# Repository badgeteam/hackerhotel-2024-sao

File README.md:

# HackerHotel 2024 stuff

Untested, might explode, you've been warned.

## License

The artwork featured in this hardware design has been designed by Nikolett S. from tilde.industries.

The electronics have been designed by Renze Nicolai from Nicolai Electronics.

This hardware design may be used under the terms of the [CERN-OHL-P](LICENSE) license.

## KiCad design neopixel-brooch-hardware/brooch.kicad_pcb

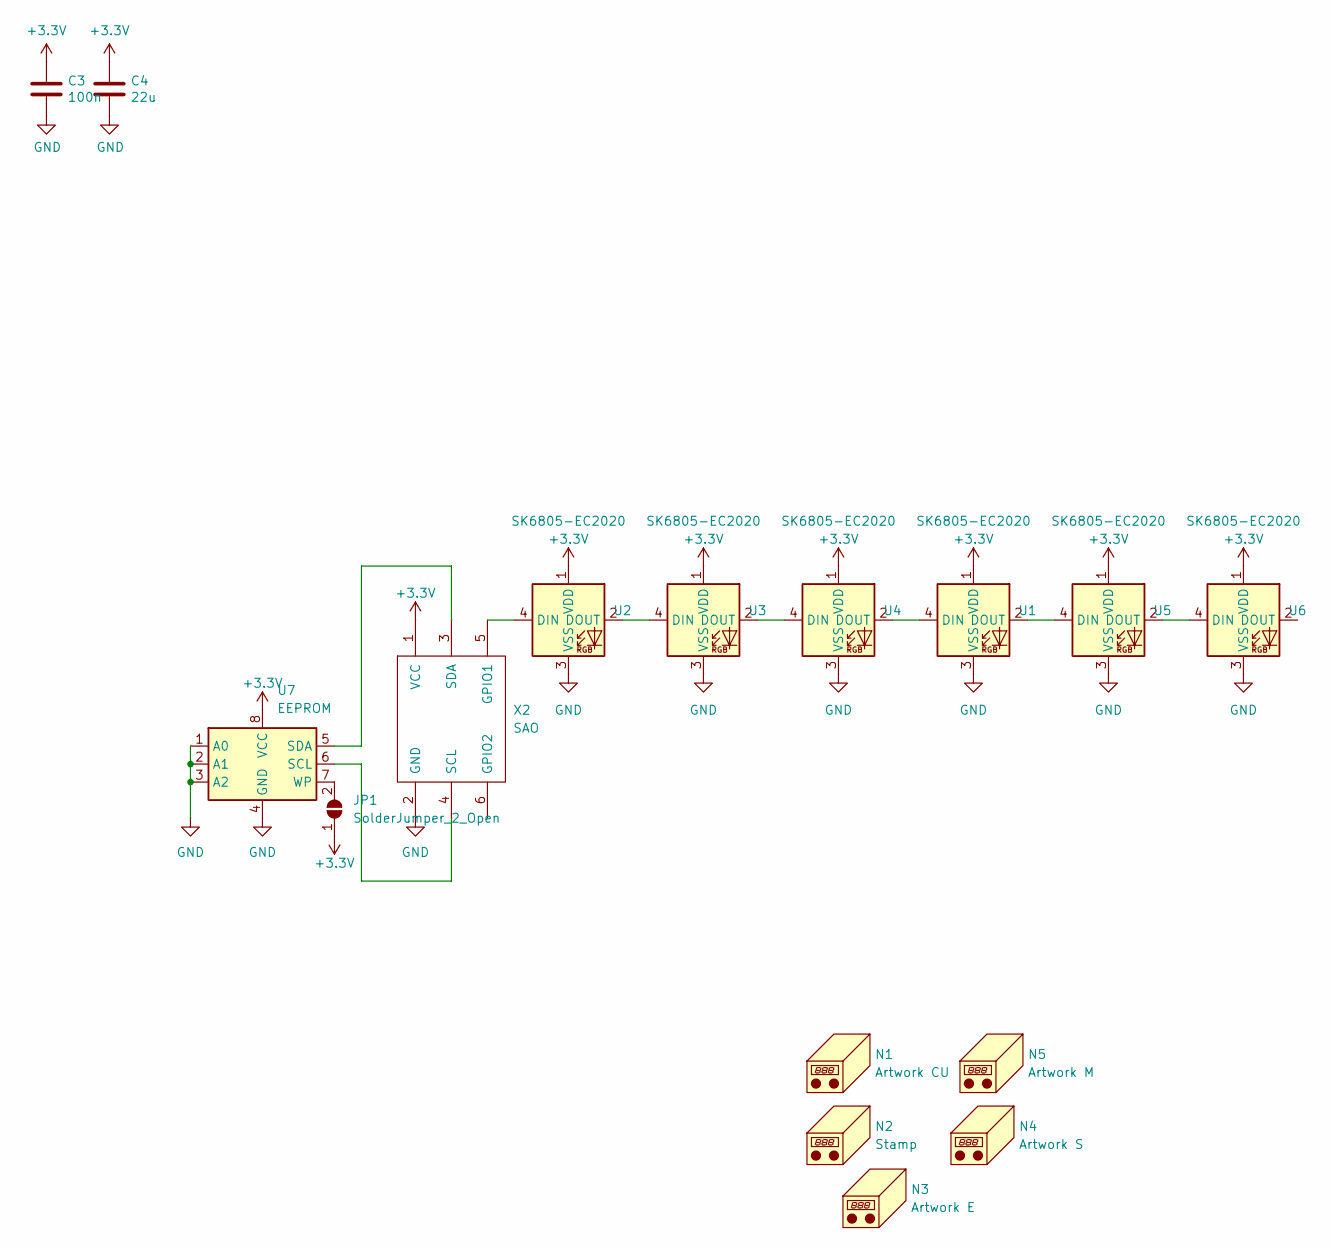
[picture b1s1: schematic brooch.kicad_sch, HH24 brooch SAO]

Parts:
C3: 100n; C_0402_1005Metric; LCSC C307331
C4: 22u; C_0805_2012Metric; LCSC C602037
JP1: SolderJumper_2_Open; SolderJumper-2_P1.3mm_Open_Pad1.0x1.5mm
N1: Artwork CU; Brooch_LED_F.Cu
N2: Stamp; stamp
N3: Artwork E; Brooch_EdgeCut
N4: Artwork S; Brooch_F.SilkS
N5: Artwork M; Brooch_F.Mask
U1, U2, U3, U4, U5, U6: SK6805-EC2020; SK6805-EC20; LCSC C2890036
U7: EEPROM; SOIC-8_3.9x4.9mm_P1.27mm
X2: SAO; PinHeader_2x03_P2.54mm_Vertical_SMD

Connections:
+3.3V: C3.1, C4.1, JP1.1 (A), U1.1 (VDD), U2.1 (VDD), U3.1 (VDD), U4.1 (VDD), U5.1 (VDD), U6.1 (VDD), U7.8 (VCC), X2.1 (VCC)
GND: C3.2, C4.2, U1.3 (VSS), U2.3 (VSS), U3.3 (VSS), U4.3 (VSS), U5.3 (VSS), U6.3 (VSS), U7.1 (A0), U7.2 (A1), U7.3 (A2), U7.4 (GND), X2.2 (GND)
unnamed: JP1.2 (B), U7.7 (WP)
unnamed: U1.4 (DIN), U4.2 (DOUT)
unnamed: U1.2 (DOUT), U5.4 (DIN)
unnamed: U2.4 (DIN), X2.5 (GPIO1)
unnamed: U2.2 (DOUT), U3.4 (DIN)
unnamed: U3.2 (DOUT), U4.4 (DIN)
unnamed: U5.2 (DOUT), U6.4 (DIN)
unnamed: U7.6 (SCL), X2.4 (SCL)
unnamed: U7.5 (SDA), X2.3 (SDA)

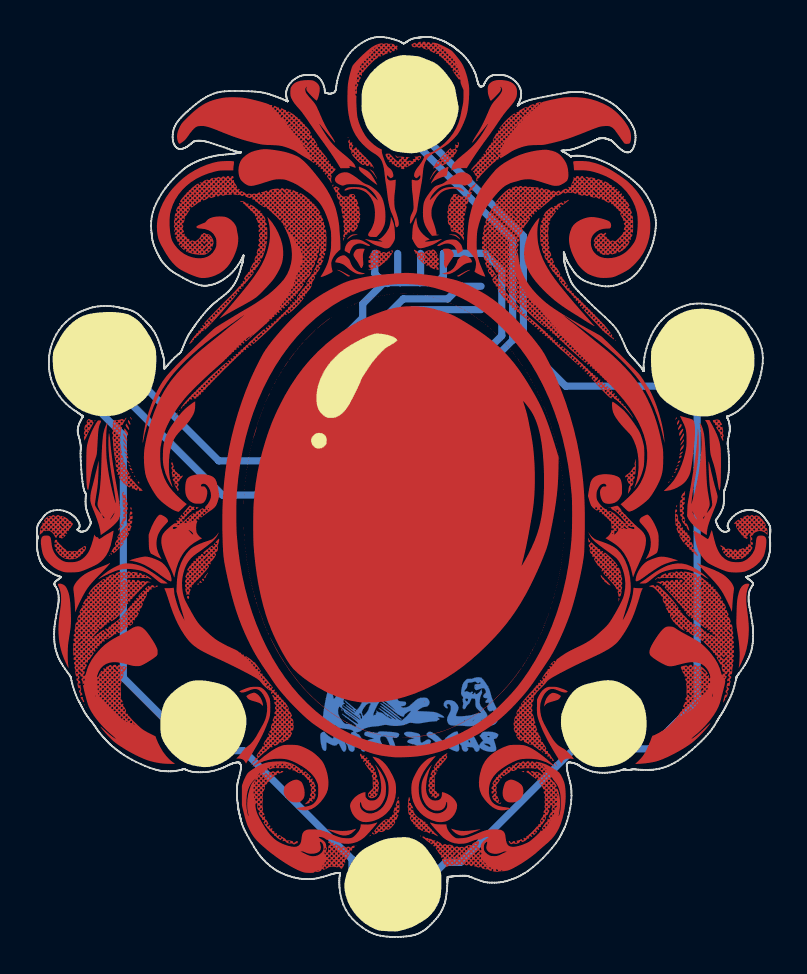
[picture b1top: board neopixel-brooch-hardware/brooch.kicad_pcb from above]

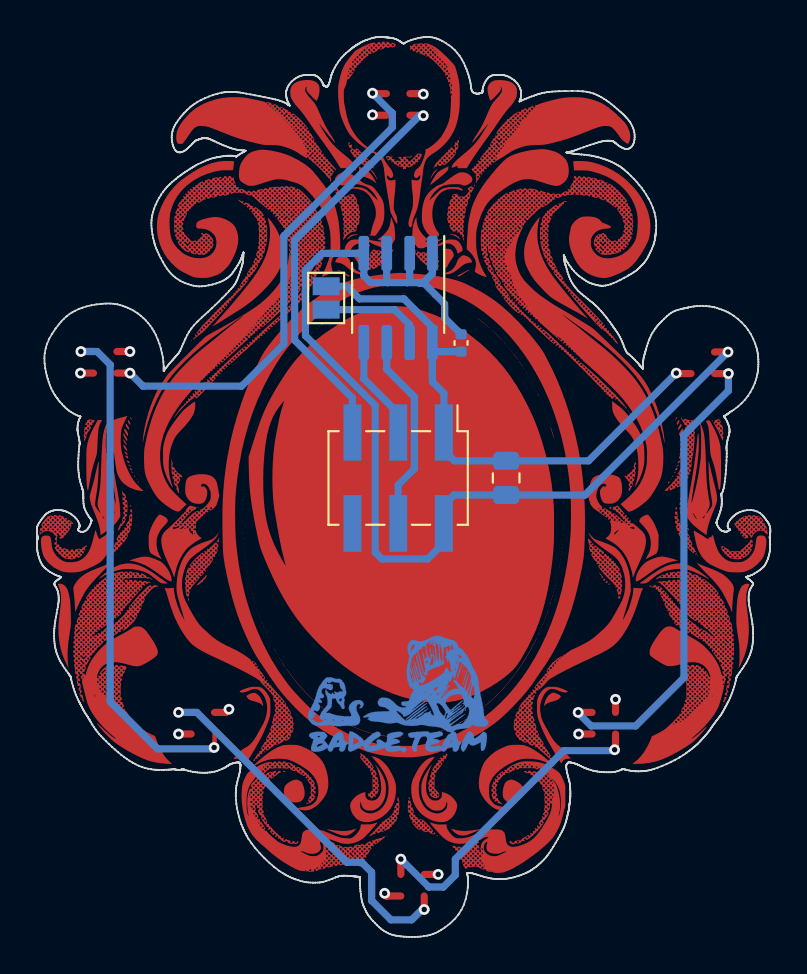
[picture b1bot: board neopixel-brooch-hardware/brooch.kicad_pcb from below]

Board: 4 copper layers, 40.7 x 50.0 mm, 16 parts (6 on the bottom side), 11 nets.

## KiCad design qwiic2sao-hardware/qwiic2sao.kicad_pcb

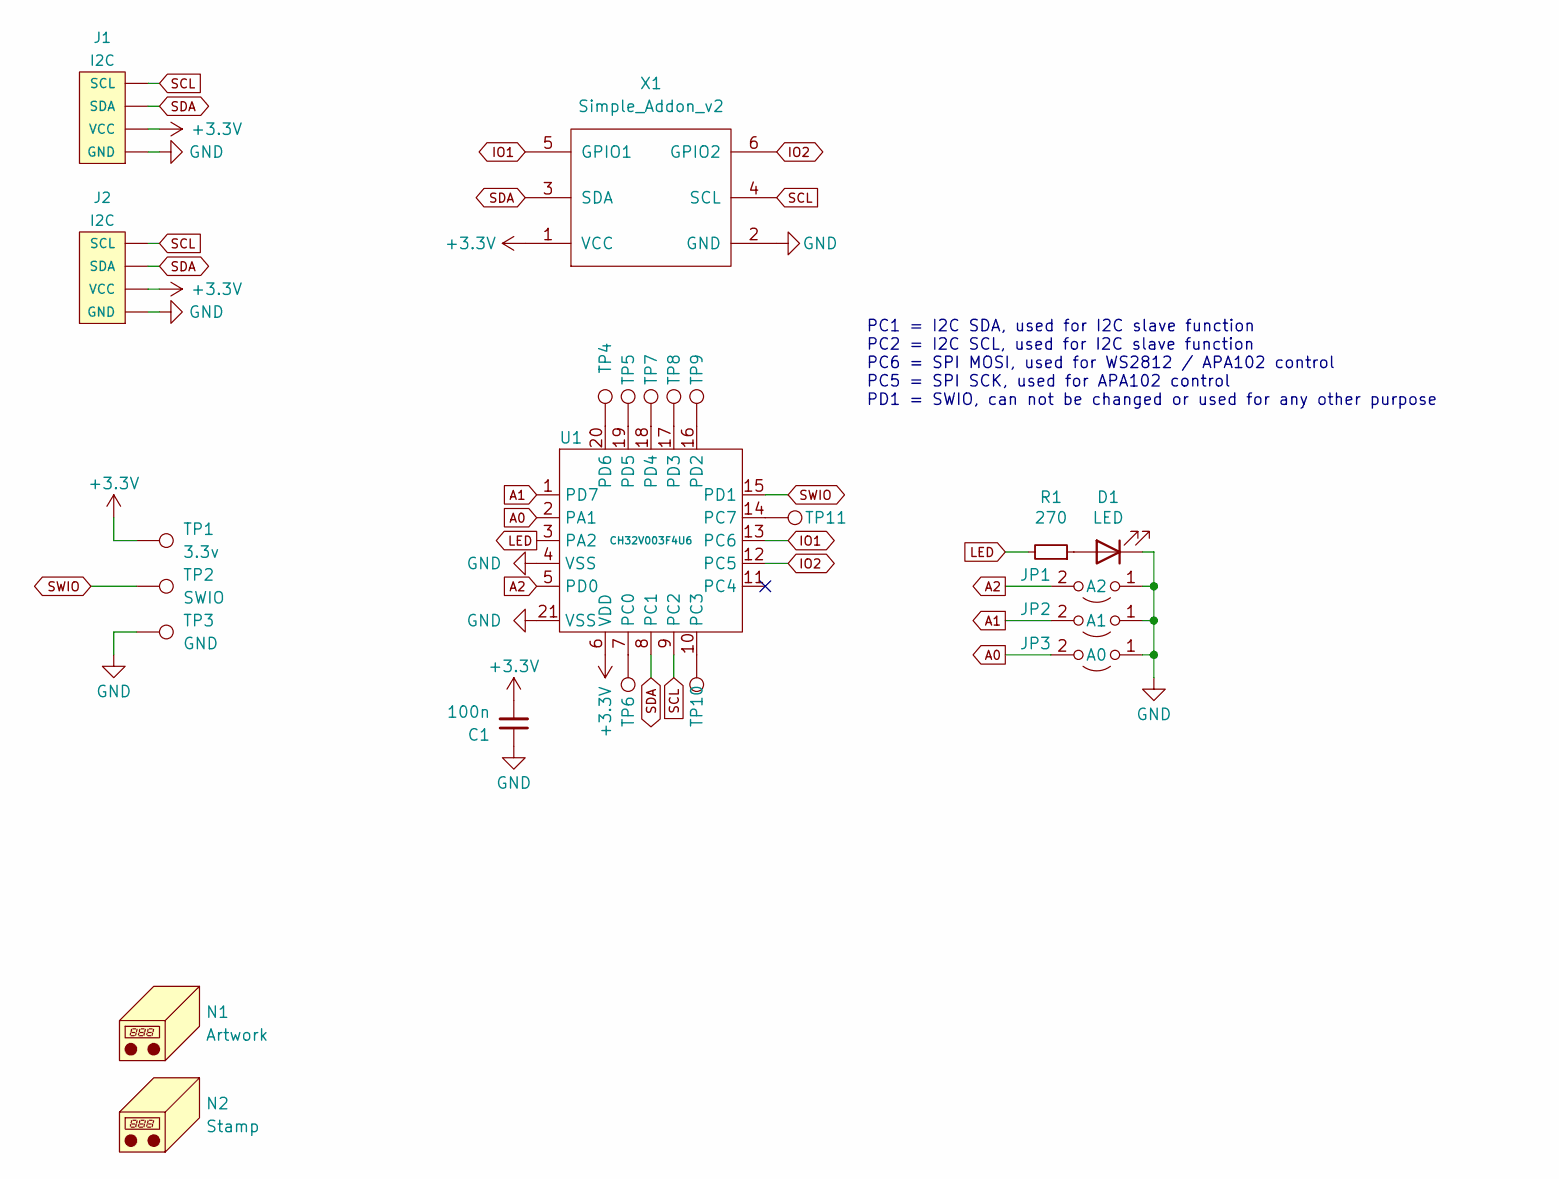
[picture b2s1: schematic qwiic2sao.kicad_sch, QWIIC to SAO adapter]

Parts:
C1: 100n; C_0402_1005Metric
D1: LED; LED_0603_1608Metric; LCSC C264473
J1, J2: I2C; 1X04_1MM_RA_GND; LCSC C160404
JP1: A2; SolderJumper-2_P1.3mm_Open_TrianglePad1.0x1.5mm
JP2: A1; SolderJumper-2_P1.3mm_Open_TrianglePad1.0x1.5mm
JP3: A0; SolderJumper-2_P1.3mm_Open_TrianglePad1.0x1.5mm
N1: Artwork; artwork
N2: Stamp; stamp
R1: 270; R_0402_1005Metric; LCSC C22966
TP1: 3.3v; TestPoint_Pad_D2.0mm
TP2: SWIO; TestPoint_Pad_D2.0mm
TP3: GND; TestPoint_Pad_D2.0mm
TP4, TP5, TP7, TP8, TP9: TestPoint_Pad_D2.0mm
TP6, TP10: TestPoint_Pad_D1.0mm
TP11: 14; TestPoint_Pad_D2.0mm
U1: CH32V003F4U6; QFN-20-1EP_3x3mm_P0.4mm_EP1.65x1.65mm; LCSC C5299908
X1: Simple_Addon_v2; Simple_Addon_v2-BADGE-2x3

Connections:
+3.3V: C1.2, J1.2 (VCC), J2.2 (VCC), TP1.1, U1.6 (VDD), X1.1 (VCC)
A0: JP3.2 (B), U1.2 (PA1)
A1: JP2.2 (B), U1.1 (PD7)
A2: JP1.2 (B), U1.5 (PD0)
GND: C1.1, D1.1 (K), J1.1 (GND), J1.5, J1.6, J2.1 (GND), J2.5, J2.6, JP1.1 (A), JP2.1 (A), JP3.1 (A), TP3.1, U1.4 (VSS), U1.21 (VSS), X1.2 (GND)
IO1: U1.13 (PC6), X1.5 (GPIO1)
IO2: U1.12 (PC5), X1.6 (GPIO2)
LED: R1.2, U1.3 (PA2)
unnamed: D1.2 (A), R1.1
unnamed: TP6.1, U1.7 (PC0)
unnamed: TP10.1, U1.10 (PC3)
unnamed: TP11.1, U1.14 (PC7)
unnamed: TP9.1, U1.16 (PD2)
unnamed: TP8.1, U1.17 (PD3)
unnamed: TP7.1, U1.18 (PD4)
unnamed: TP5.1, U1.19 (PD5)
unnamed: TP4.1, U1.20 (PD6)
SCL: J1.4 (SCL), J2.4 (SCL), U1.9 (PC2), X1.4 (SCL)
SDA: J1.3 (SDA), J2.3 (SDA), U1.8 (PC1), X1.3 (SDA)
SWIO: TP2.1, U1.15 (PD1)

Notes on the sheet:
PC1 = I2C SDA, used for I2C slave function PC2 = I2C SCL, used for I2C slave function PC6 = SPI MOSI, used for WS2812 / APA102 control PC5 = SPI SCK, used for APA102 control PD1 = SWIO, can not be changed or used for any other purpose

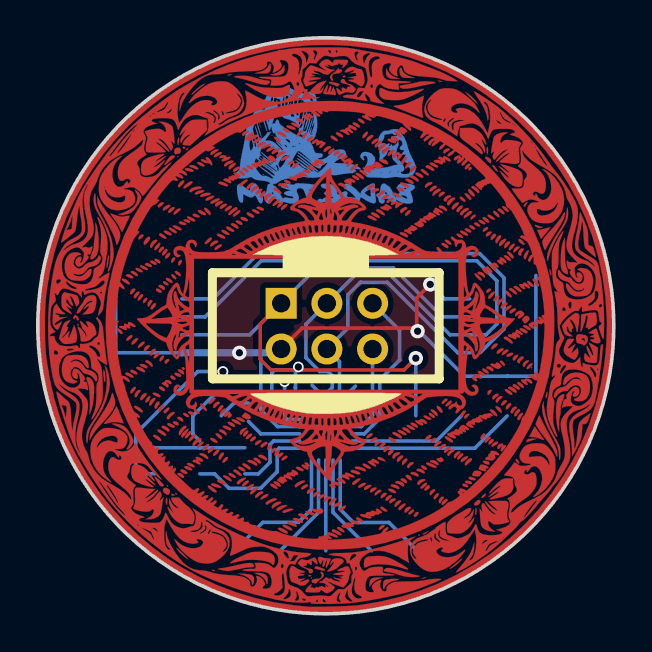
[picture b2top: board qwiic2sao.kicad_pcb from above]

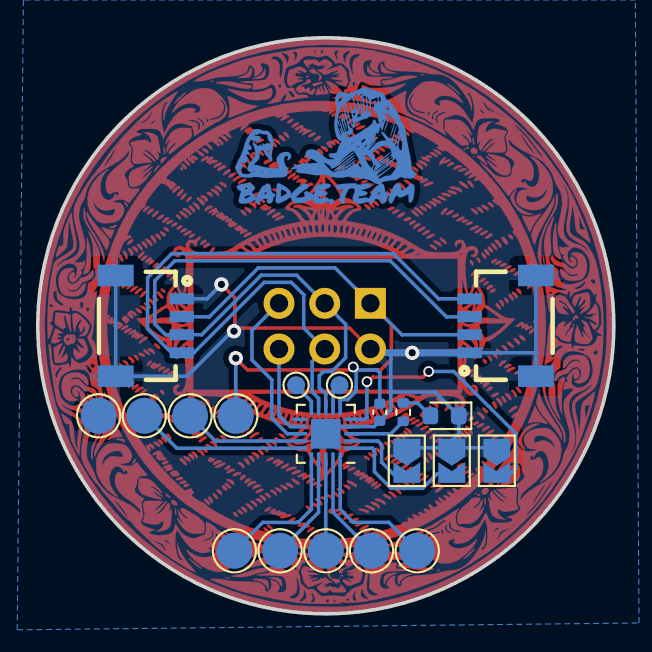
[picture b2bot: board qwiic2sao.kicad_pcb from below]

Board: 2 copper layers, 32.0 x 32.0 mm, 23 parts (21 on the bottom side), 20 nets.

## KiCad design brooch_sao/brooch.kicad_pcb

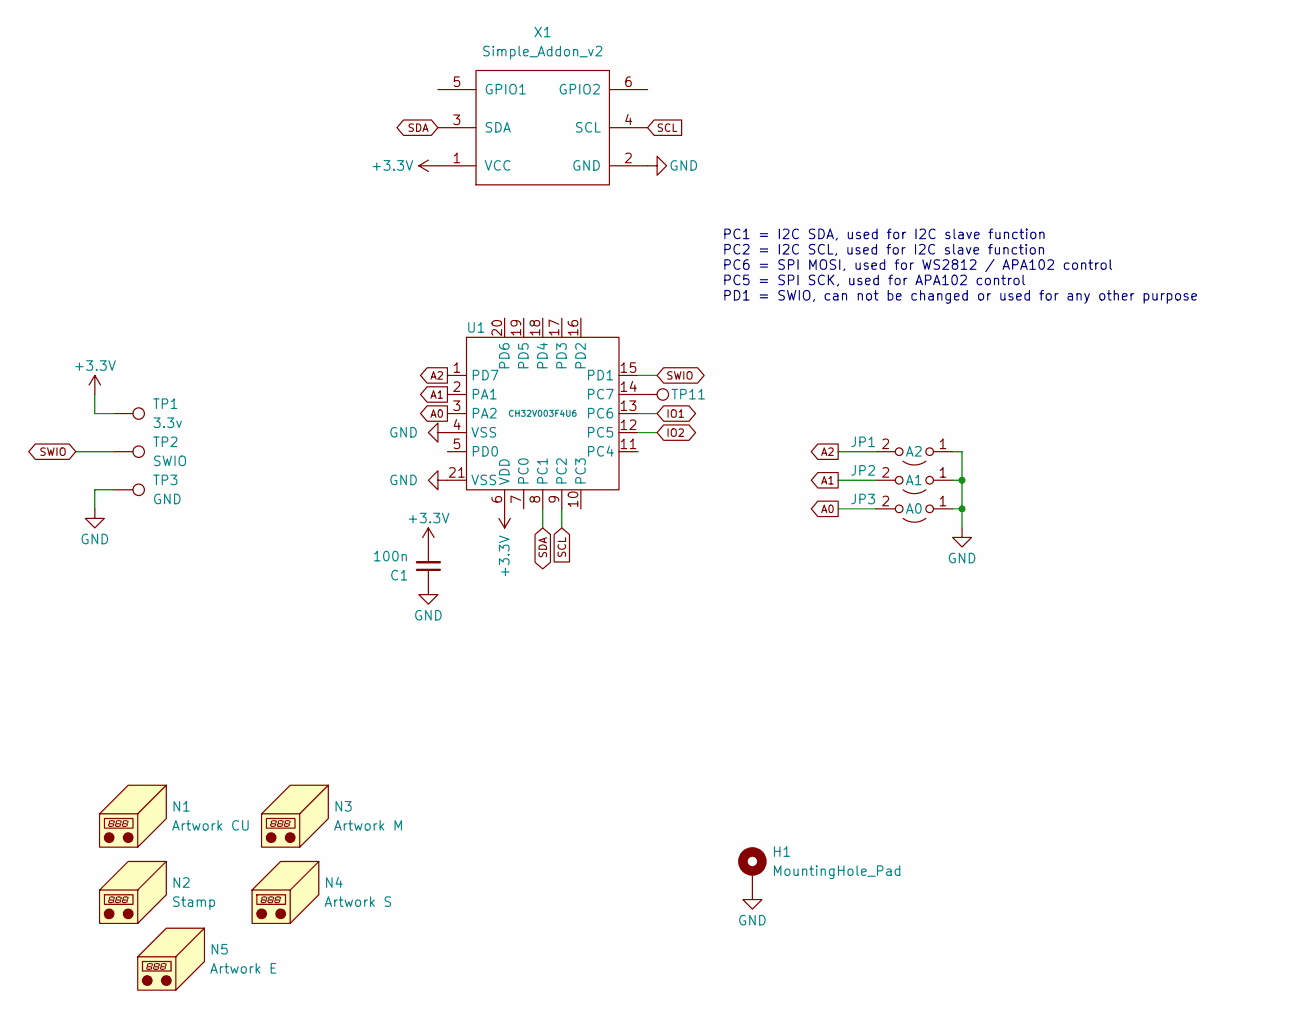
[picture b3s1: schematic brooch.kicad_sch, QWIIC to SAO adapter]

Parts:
C1: 100n; C_0402_1005Metric
H1: MountingHole_Pad; TestPoint_Pad_D5.0mm
JP1: A2; SolderJumper-2_P1.3mm_Open_TrianglePad1.0x1.5mm
JP2: A1; SolderJumper-2_P1.3mm_Open_TrianglePad1.0x1.5mm
JP3: A0; SolderJumper-2_P1.3mm_Open_TrianglePad1.0x1.5mm
N1: Artwork CU; Brooch_F.Cu
N2: Stamp; stamp
N3: Artwork M; Brooch_F.Mask
N4: Artwork S; Brooch_F.SilkS
N5: Artwork E; Brooch_EdgeCut
TP1: 3.3v; TestPoint_Pad_D2.0mm
TP2: SWIO; TestPoint_Pad_D2.0mm
TP3: GND; TestPoint_Pad_D2.0mm
TP11: 14; TestPoint_Pad_D2.0mm
U1: CH32V003F4U6; QFN-20-1EP_3x3mm_P0.4mm_EP1.65x1.65mm; LCSC C5299908
X1: Simple_Addon_v2; PinHeader_2x03_P2.54mm_Vertical_SMD

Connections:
+3.3V: C1.2, TP1.1, U1.6 (VDD), X1.1 (VCC)
A0: JP3.2 (B), U1.3 (PA2)
A1: JP2.2 (B), U1.2 (PA1)
A2: JP1.2 (B), U1.1 (PD7)
GND: C1.1, H1.1, JP1.1 (A), JP2.1 (A), JP3.1 (A), TP3.1, U1.4 (VSS), U1.21 (VSS), X1.2 (GND)
IO1: U1.13 (PC6)
IO2: U1.12 (PC5)
unnamed: TP11.1, U1.14 (PC7)
SCL: U1.9 (PC2), X1.4 (SCL)
SDA: U1.8 (PC1), X1.3 (SDA)
SWIO: TP2.1, U1.15 (PD1)

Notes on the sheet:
PC1 = I2C SDA, used for I2C slave function PC2 = I2C SCL, used for I2C slave function PC6 = SPI MOSI, used for WS2812 / APA102 control PC5 = SPI SCK, used for APA102 control PD1 = SWIO, can not be changed or used for any other purpose

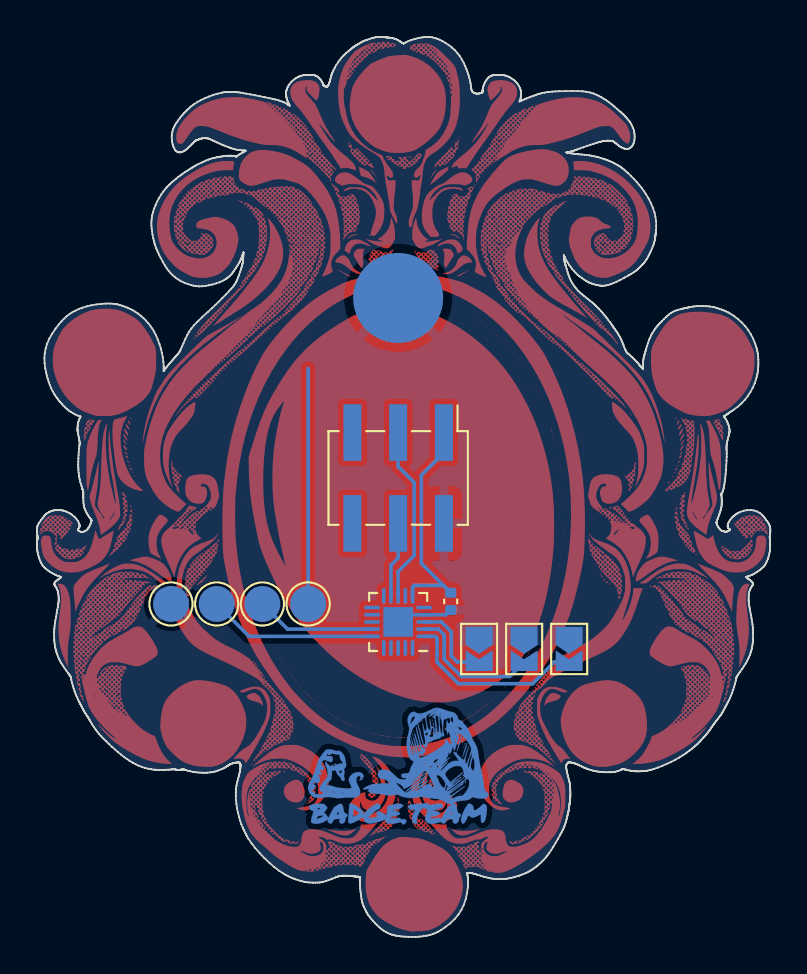
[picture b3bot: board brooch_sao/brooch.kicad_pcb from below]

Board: 2 copper layers, 40.7 x 50.0 mm, 16 parts (12 on the bottom side), 9 nets.

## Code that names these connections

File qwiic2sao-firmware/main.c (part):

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#define I2C_ADDR 0x43

// Address selection jumper pins
#define PIN_AJ0 PA1
#define PIN_AJ1 PD7
#define PIN_AJ2 PD0

// LED pin
#define PIN_LED PA2

// I2C interface pins
#define PIN_SDA PC1
#define PIN_SCL PC2

// SAO GPIO pins
#define PIN_IO1 PC6
#define PIN_IO2 PC5

// GPIO pins on row of testpads
#define PIN_IOA PD2
#define PIN_IOB PD3
#define PIN_IOC PD4
#define PIN_IOD PD5
#define PIN_IOE PD6

// Other GPIO pins
#define PIN_EXT PC7
#define PIN_TP1 PC3
#define PIN_TP6 PC0

// I2C registers
#define I2C_REG_FW_VERSION_0      0  // LSB
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
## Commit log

2024-01-12 Stuff.
2024-03-08 Add firmware, move hardware
